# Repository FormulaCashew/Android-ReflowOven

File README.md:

# Reflow Oven Controller

An Android application built with Jetpack Compose and Kotlin to monitor and control a DIY Reflow Oven. The application is designed to communicate via TCP sockets with an ESP32 or any WiFi-enabled microcontroller.

The system uses a microcontroller to facilitate Closed-Loop PID control. It utilizes a controlled rectifier PCB to regulate power delivered to the oven and measures temperature using a thermocouple.

## Project Structure

*   **Application/**: Contains the Android application source code.
*   **Hardware/**: Contains schematics and PCB designs for the controlled rectifier and measurement circuits.
*   **Firmware/**: Contains the code for the microcontroller.
*   **test/**: Contains a script to simulate the behavior of the microcontroller for testing the app without hardware.

## Features

*   **Real-Time Monitoring**: Visualizes temperature curves.
*   **Profile Management**: Supports custom and pre-defined soldering profiles.
*   **Device Control**: Start, Stop, and status monitoring commands.

## Architecture

The Android app follows Clean Architecture and MVVM principles using:
*   **UI**: Jetpack Compose (Material 3)
*   **Async**: Kotlin Coroutines & Flows
*   **Charting**: MPAndroidChart

## Communication Protocol

The App acts as a TCP Client connecting to the microcontroller (Server).

**Commands (App -> Microcontroller)**
*   `STATUS?`: Request current status.
*   `START;{soak_temp};{soak_time};{reflow_temp};{reflow_time}`: Begin feedback loop with parameters.
*   `STOP`: Stop the process.

**Response**
*   `STATUS;{current_temp};{target_temp};{state};{timer}`

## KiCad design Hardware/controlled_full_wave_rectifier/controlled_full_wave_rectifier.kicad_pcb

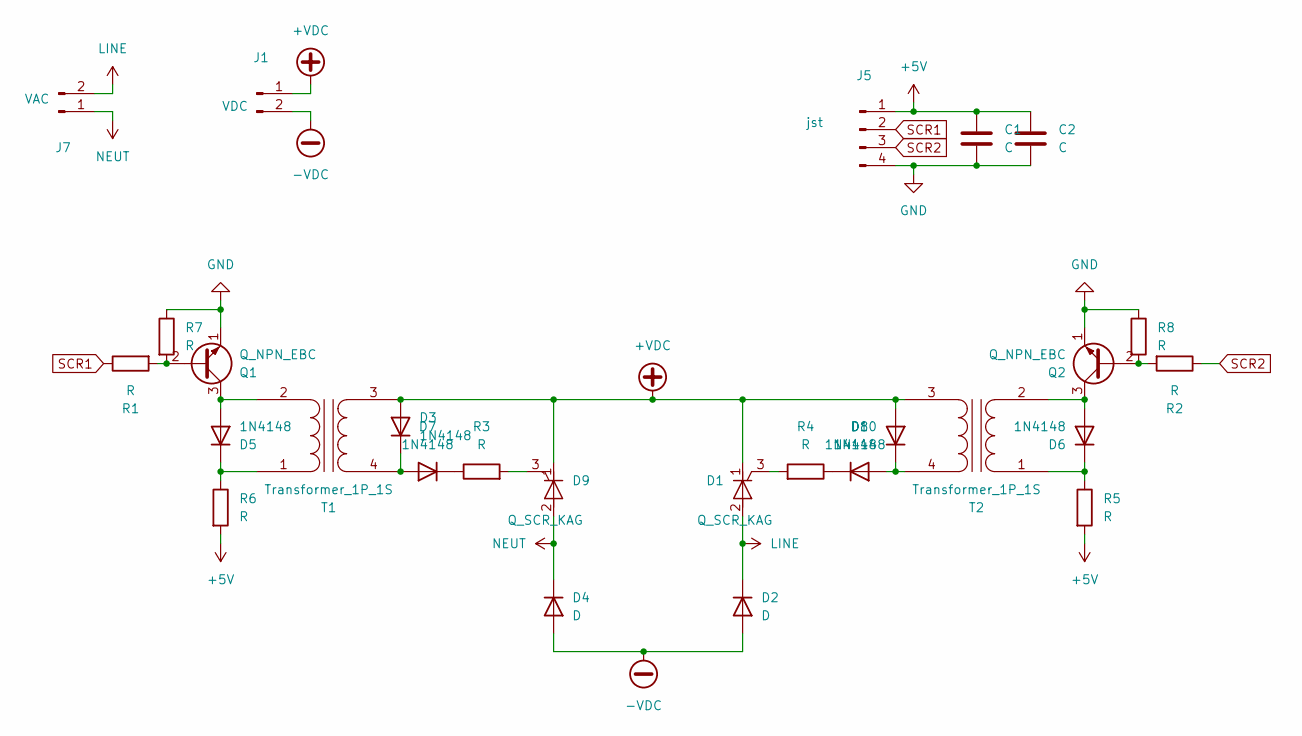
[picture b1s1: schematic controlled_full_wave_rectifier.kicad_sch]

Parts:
C1, C2: C; C_Disc_D4.3mm_W1.9mm_P5.00mm
D1, D9: Q_SCR_KAG; TO-220-3_Vertical
D2, D4: D; TO-220-2_Vertical
D3, D5, D6, D7, D8, D10: 1N4148; D_DO-35_SOD27_P7.62mm_Horizontal
J1: VDC; PhoenixContact_MCV_1,5_2-G-5.08_1x02_P5.08mm_Vertical
J5: jst; Molex_KK-254_AE-6410-04A_1x04_P2.54mm_Vertical
J7: VAC; PhoenixContact_MCV_1,5_2-G-5.08_1x02_P5.08mm_Vertical
Q1, Q2: Q_NPN_EBC; TO-92
R1, R2, R3, R4, R5, R6, R7, R8: R; R_Axial_DIN0207_L6.3mm_D2.5mm_P7.62mm_Horizontal
T1, T2: Transformer_1P_1S; Transformer_Toroid_Horizontal_D14.0mm_Amidon-T50

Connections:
+5V: C1.1, C2.1, J5.1, R5.2, R6.2
+VDC: D1.1 (K), D3.2 (A), D9.1 (K), D10.2 (A), J1.1, T1.3 (SA), T2.3 (SA)
-VDC: D2.2 (A), D4.2 (A), J1.2
GND: C1.2, C2.2, J5.4, Q1.1 (E), Q2.1 (E), R7.1, R8.1
LINE: D1.2 (A), D2.1 (K), J7.2
NEUT: D4.1 (K), D9.2 (A), J7.1
unnamed: D1.3 (G), R4.2
unnamed: D3.1 (K), D7.2 (A), T1.4 (SB)
unnamed: D5.2 (A), Q1.3 (C), T1.2 (AB)
unnamed: D5.1 (K), R6.1, T1.1 (AA)
unnamed: D6.2 (A), Q2.3 (C), T2.2 (AB)
unnamed: D6.1 (K), R5.1, T2.1 (AA)
unnamed: D7.1 (K), R3.1
unnamed: D8.1 (K), R4.1
unnamed: D9.3 (G), R3.2
unnamed: D8.2 (A), D10.1 (K), T2.4 (SB)
unnamed: Q1.2 (B), R1.2, R7.2
unnamed: Q2.2 (B), R2.2, R8.2
SCR1: J5.2, R1.1
SCR2: J5.3, R2.1

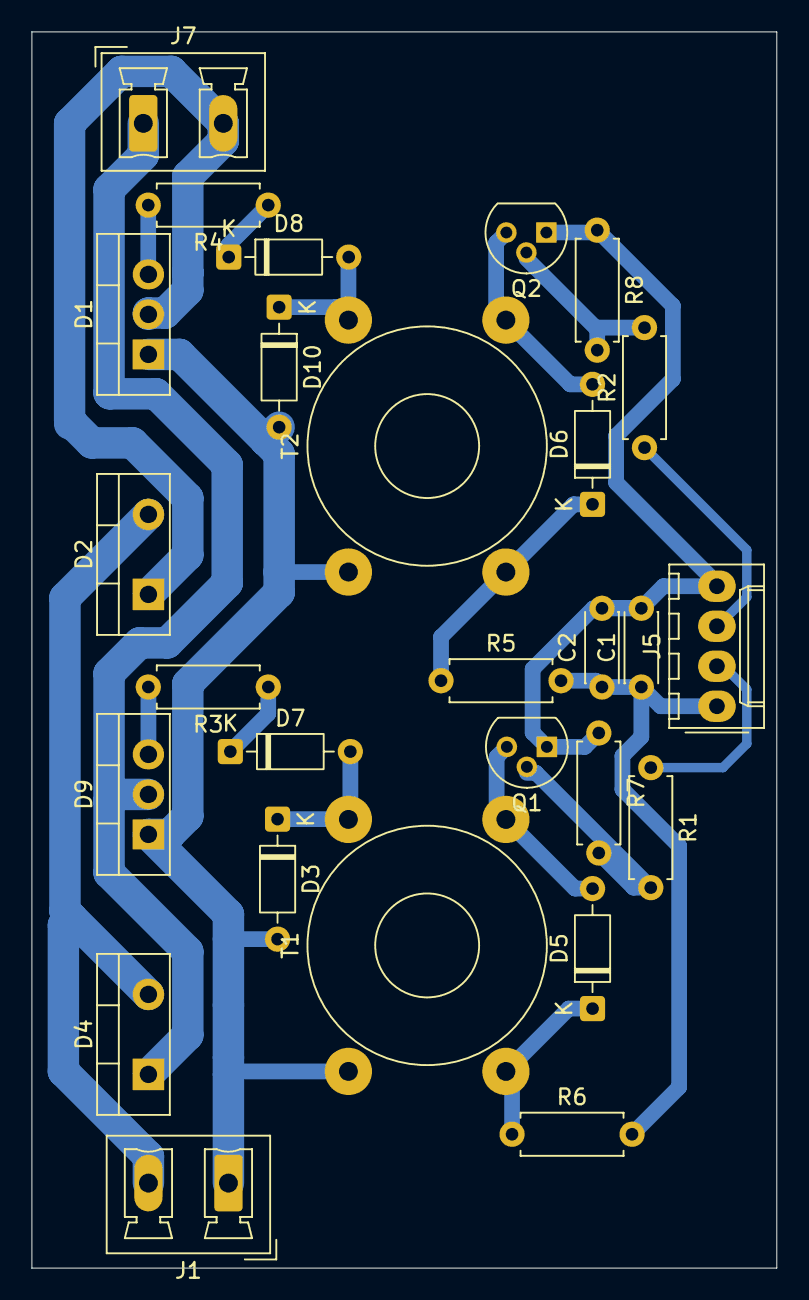
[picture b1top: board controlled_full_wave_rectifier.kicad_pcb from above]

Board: 2 copper layers, 47.3 x 78.5 mm, 27 parts (0 on the bottom side), 20 nets.

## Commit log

2025-11-11 ActaConstitucion
2025-11-11 Cronograma
2025-12-08 initial app commit
2025-12-08 Added class for showing a data chart
2025-12-08 Updated code to include data chart to graph data
2025-12-08 Updated code structure
2025-12-08 Add test dependencies
2025-12-08 Added tests
2025-12-08 Firmware ESP32
2025-12-08 Add README
2025-12-08 Renamed folders
2025-12-09 Changed file structure
2025-12-09 Add gitignore for files generated when compiling
2025-12-10 ReporteV1
2025-12-10 Added info about the callback hierarchy when some buttons are pressed and some info about the comms protocol
2025-12-10 final report part
2025-12-10 Added pdf report
